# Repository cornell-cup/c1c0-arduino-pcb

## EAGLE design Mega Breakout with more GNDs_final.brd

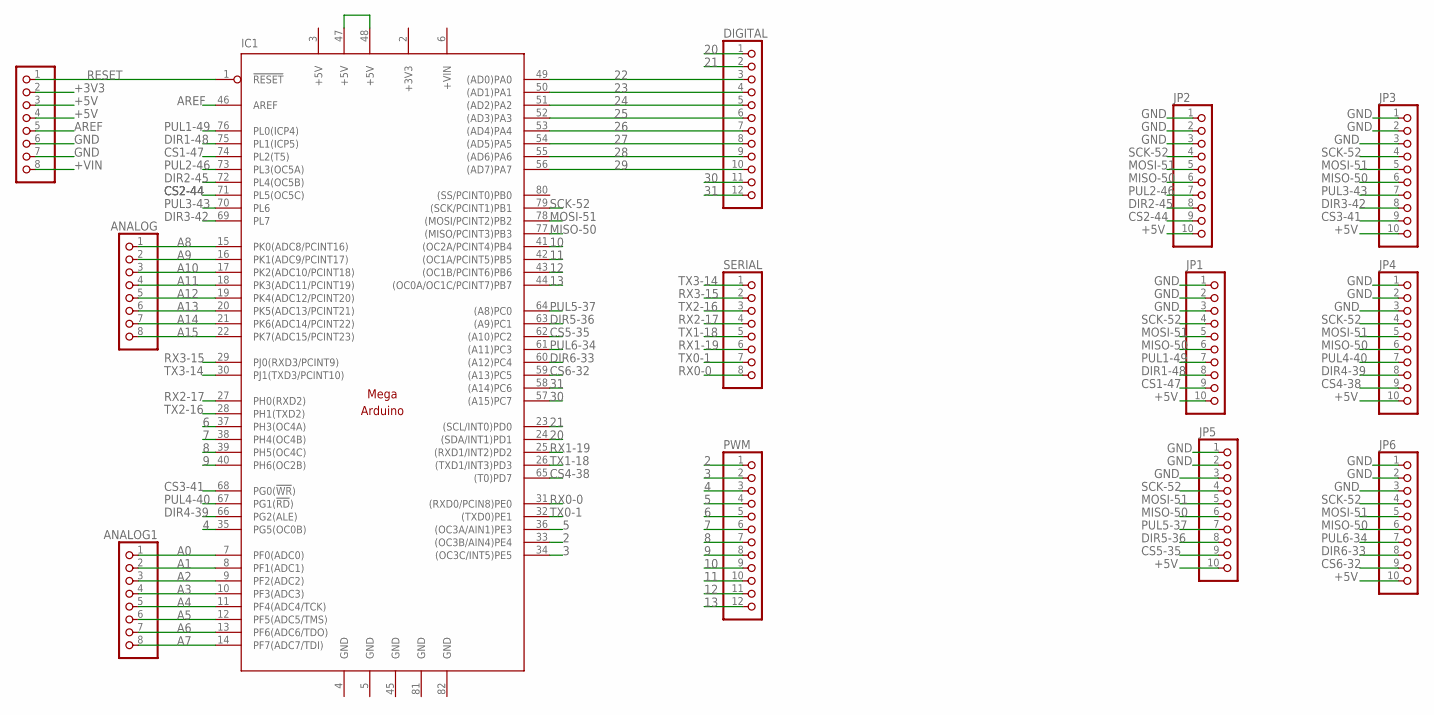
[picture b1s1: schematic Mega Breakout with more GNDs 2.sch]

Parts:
ANALOG, ANALOG1: PINHD-1X8; 1X08
DIGITAL: PINHD-1X12; 1X12
IC1: MEGAARDUINO_1; MEGA_ARDUINO
JP1, JP2, JP3, JP4, JP5, JP6: PINHD-1X10; 1X10
POWER: PINHD-1X8; 1X08
PWM: PINHD-1X12; 1X12
SERIAL: PINHD-1X8; 1X08

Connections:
2: IC1.33 ((OC3B/AIN4)PE4), PWM.1
3: IC1.34 ((OC3C/INT5)PE5), PWM.2
4: IC1.35 (PG5(OC0B)), PWM.3
5: IC1.36 ((OC3A/AIN1)PE3), PWM.4
6: IC1.37 (PH3(OC4A)), PWM.5
7: IC1.38 (PH4(OC4B)), PWM.6
8: IC1.39 (PH5(OC4C)), PWM.7
9: IC1.40 (PH6(OC2B)), PWM.8
10: IC1.41 ((OC2A/PCINT4)PB4), PWM.9
11: IC1.42 ((OC1A/PCINT5)PB5), PWM.10
12: IC1.43 ((OC1B/PCINT6)PB6), PWM.11
13: IC1.44 ((OC0A/OC1C/PCINT7)PB7), PWM.12
20: DIGITAL.1, IC1.24 ((SDA/INT1)PD1)
21: DIGITAL.2, IC1.23 ((SCL/INT0)PD0)
22: DIGITAL.3, IC1.49 ((AD0)PA0)
23: DIGITAL.4, IC1.50 ((AD1)PA1)
24: DIGITAL.5, IC1.51 ((AD2)PA2)
25: DIGITAL.6, IC1.52 ((AD3)PA3)
26: DIGITAL.7, IC1.53 ((AD4)PA4)
27: DIGITAL.8, IC1.54 ((AD5)PA5)
28: DIGITAL.9, IC1.55 ((AD6)PA6)
29: DIGITAL.10, IC1.56 ((AD7)PA7)
30: DIGITAL.11, IC1.57 ((A15)PC7)
31: DIGITAL.12, IC1.58 ((A14)PC6)
+3V3: IC1.2 (+3V3), POWER.2
+5V: IC1.3 (+5V), JP1.10, JP2.10, JP3.10, JP4.10, JP5.10, JP6.10, POWER.3, POWER.4
+VIN: IC1.6 (+VIN), POWER.8
A0: ANALOG1.1, IC1.7 (PF0(ADC0))
A1: ANALOG1.2, IC1.8 (PF1(ADC1))
A2: ANALOG1.3, IC1.9 (PF2(ADC2))
A3: ANALOG1.4, IC1.10 (PF3(ADC3))
A4: ANALOG1.5, IC1.11 (PF4(ADC4/TCK))
A5: ANALOG1.6, IC1.12 (PF5(ADC5/TMS))
A6: ANALOG1.7, IC1.13 (PF6(ADC6/TDO))
A7: ANALOG1.8, IC1.14 (PF7(ADC7/TDI))
A8: ANALOG.1, IC1.15 (PK0(ADC8/PCINT16))
A9: ANALOG.2, IC1.16 (PK1(ADC9/PCINT17))
A10: ANALOG.3, IC1.17 (PK2(ADC10/PCINT18))
A11: ANALOG.4, IC1.18 (PK3(ADC11/PCINT19))
A12: ANALOG.5, IC1.19 (PK4(ADC12/PCINT20))
A13: ANALOG.6, IC1.20 (PK5(ADC13/PCINT21))
A14: ANALOG.7, IC1.21 (PK6(ADC14/PCINT22))
A15: ANALOG.8, IC1.22 (PK7(ADC15/PCINT23))
AREF: IC1.46 (AREF), POWER.5
CS1-47: IC1.74 (PL2(T5)), JP1.9
CS2-44: IC1.71 (PL5(OC5C)), JP2.9
CS3-41: IC1.68 (PG0(!WR!)), JP3.9
CS4-38: IC1.65 ((T0)PD7), JP4.9
CS5-35: IC1.62 ((A10)PC2), JP5.9
CS6-32: IC1.59 ((A13)PC5), JP6.9
DIR1-48: IC1.75 (PL1(ICP5)), JP1.8
DIR2-45: IC1.72 (PL4(OC5B)), JP2.8
DIR3-42: IC1.69 (PL7), JP3.8
DIR4-39: IC1.66 (PG2(ALE)), JP4.8
DIR5-36: IC1.63 ((A9)PC1), JP5.8
DIR6-33: IC1.60 ((A12)PC4), JP6.8
GND: IC1.4 (GND), IC1.5 (GND), IC1.45 (GND), IC1.81 (GND), IC1.82 (GND), JP1.1, JP1.2, JP1.3, JP2.1, JP2.2, JP2.3, JP3.1, JP3.2, JP3.3, JP4.1, JP4.2, JP4.3, JP5.1, JP5.2, JP5.3, JP6.1, JP6.2, JP6.3, POWER.6, POWER.7
MISO-50: IC1.77 ((MISO/PCINT3)PB3), JP1.6, JP2.6, JP3.6, JP4.6, JP5.6, JP6.6
MOSI-51: IC1.78 ((MOSI/PCINT2)PB2), JP1.5, JP2.5, JP3.5, JP4.5, JP5.5, JP6.5
unnamed: IC1.47 (+5V), IC1.48 (+5V)
PUL1-49: IC1.76 (PL0(ICP4)), JP1.7
PUL2-46: IC1.73 (PL3(OC5A)), JP2.7
PUL3-43: IC1.70 (PL6), JP3.7
PUL4-40: IC1.67 (PG1(!RD!)), JP4.7
PUL5-37: IC1.64 ((A8)PC0), JP5.7
PUL6-34: IC1.61 ((A11)PC3), JP6.7
RESET: IC1.1 (!RESET), POWER.1
RX0-0: IC1.31 ((RXD0/PCIN8)PE0), SERIAL.8
RX1-19: IC1.25 ((RXD1/INT2)PD2), SERIAL.6
RX2-17: IC1.27 (PH0(RXD2)), SERIAL.4
RX3-15: IC1.29 (PJ0(RXD3/PCINT9)), SERIAL.2
SCK-52: IC1.79 ((SCK/PCINT1)PB1), JP1.4, JP2.4, JP3.4, JP4.4, JP5.4, JP6.4
TX0-1: IC1.32 ((TXD0)PE1), SERIAL.7
TX1-18: IC1.26 ((TXD1/INT3)PD3), SERIAL.5
TX2-16: IC1.28 (PH1(TXD2)), SERIAL.3
TX3-14: IC1.30 (PJ1(TXD3/PCINT10)), SERIAL.1

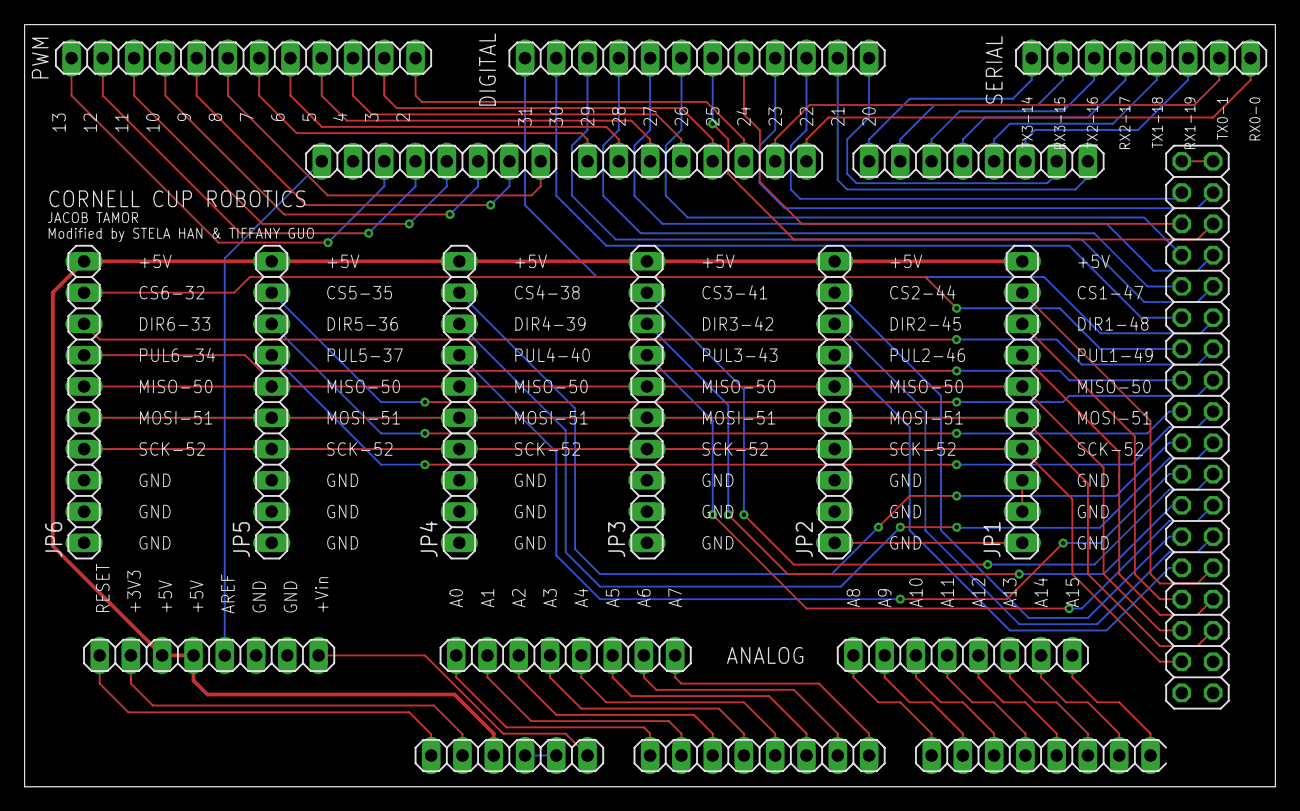
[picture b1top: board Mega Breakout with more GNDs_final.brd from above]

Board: 2 copper layers, 101.6 x 61.9 mm, 13 parts (0 on the bottom side), 76 nets.

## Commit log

2022-02-23 Add 8-header pin schematic
2022-03-10 Post-pcb review
2022-03-11 Finished PCB
2022-09-14 sem committ
2022-09-26 fixed weird angle wire
2022-09-28 final ver of modified PCB
2024-03-01 Adding screenshot of pcb
